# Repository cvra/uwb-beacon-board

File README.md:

# Universal beacon system board

This repository holds the schematics and layout of a board used as beacon localisation system for Eurobot.
It uses an Ultra-Wide Band module from Decawave and IMU.

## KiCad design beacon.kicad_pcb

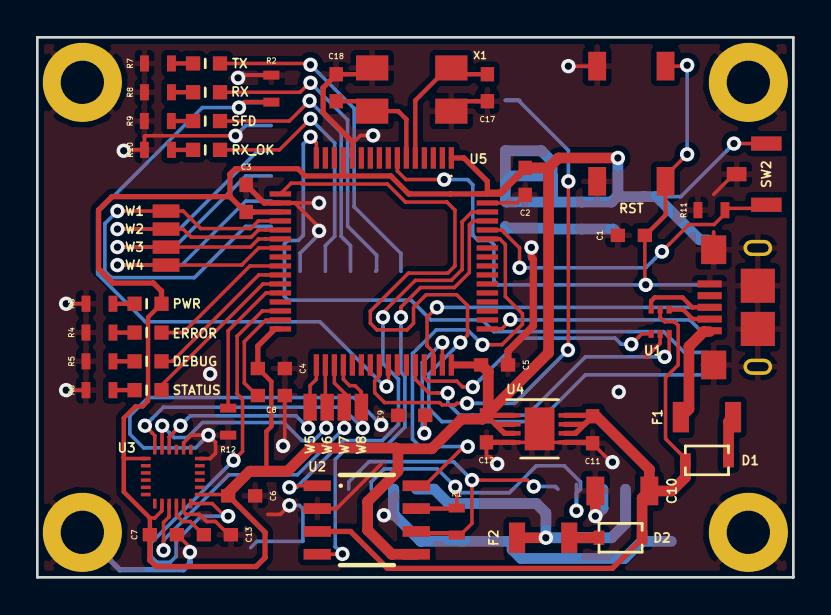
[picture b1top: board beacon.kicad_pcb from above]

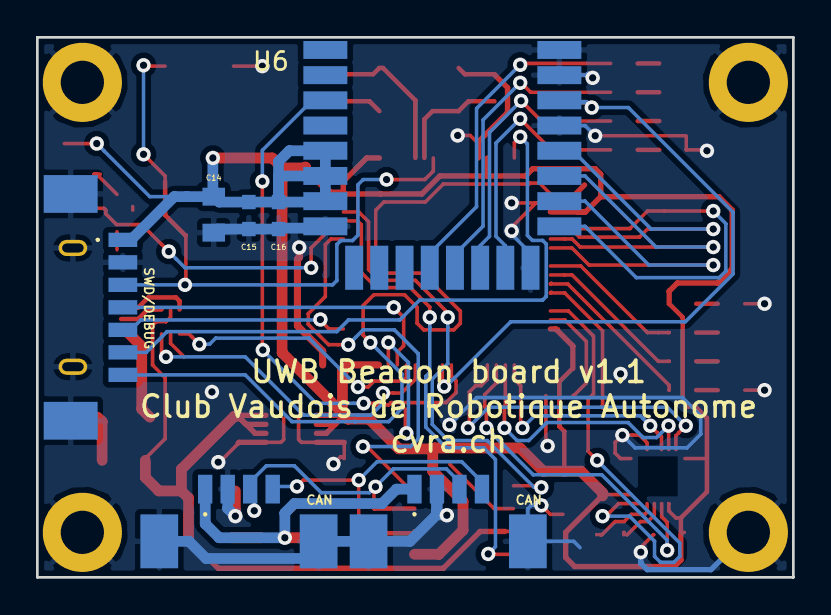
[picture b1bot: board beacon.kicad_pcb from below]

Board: 2 copper layers, 42.0 x 30.0 mm, 67 parts (7 on the bottom side), 54 nets.

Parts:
C1, C3, C4, C5, C6, C13, C16: 0.1uF; C_0603
C2, C15: 4.7uF; C_0603
C7: 10nF; C_0603
C8, C9: 2.2uF; C_0603
C10: 100uF; C_1206
C11, C12: 10uF; C_0603
C14: 47uF; C_0805
C17, C18: 10pF; C_0603
CONN1: MICRO_USB; _Micro-USB-AB-receptacle-SMT-th
CONN2, CONN3: CAN; _Molex-PicoBlade-SMD-4
CONN4: SWD/DEBUG; _Molex-PicoBlade-SMD-7
D1, D2: SBR130S3-7; _SOD-323
D3: PWR; D_0603
D4: ERROR; D_0603
D5: DEBUG; D_0603
D6: STATUS; D_0603
D7: TX; D_0603
D8: RX; D_0603
D9: SFD; D_0603
D10: RX_OK; D_0603
F1, F2: 0ZCJ0050AF2E; R_1206
H1, H2, H3, H4: M2_HOLE; _M2
R1: 120; R_0603
R2, R11, R12: 10k; R_0603
R3, R4, R5, R6, R7, R8, R9, R10: 330; R_0603
SW1: RST; _PTS525SK15-SMT-Pushbutton
SW2: DFU; SMD_Pushbutton_B3U-3100P
U1: NUF2042XV6; SOT-563_6-lead
U2: SN65HVD256; _SO-8
U3: MPU-9250; _MPU-9XX0
U4: LT1965-3.3; DFN-8-1EP_3x3mm_Pitch0.5mm
U5: STM32F405RGT6; _LQFP64
U6: DWM1000
W1: TEST_UWB_CSN; Test_1pin_SMD
W2: TEST_UWB_CLK; Test_1pin_SMD
W3, W7: TEST_UWB_MISO; Test_1pin_SMD
W4, W8: TEST_UWB_MOSI; Test_1pin_SMD
W5: TEST_IMU_CSN; Test_1pin_SMD
W6: TEST_UWB_SCK; Test_1pin_SMD
X1: 16MHz; XTAL_ABMM2

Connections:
+5V_protected: C10.1, C11.1, D1.1, D2.1, U1.5, U2.3, U4.6, U4.7, U4.8
/BOOT0: R11.2, SW2.1, U5.60
/BOOT1: R12.2, U5.28
/CAN1_RX: U2.4, U5.61
/CAN1_SILENT: U2.8, U5.59
/CAN1_TX: U2.1, U5.62
/DEBUG_LED: D5.2, U5.26
/ERROR_LED: D4.2, U5.25
/IMU_CS_N: U3.22, U5.33, W5.1
/IMU_INT: U3.12, U5.30
/IMU_MISO: U3.9, U5.35, W7.1
/IMU_MOSI: U3.24, U5.36, W8.1
/IMU_SCK: U3.23, U5.34, W6.1
/STATUS_LED: D6.2, U5.27
/STM32_NRST: C1.1, CONN4.3, SW1.2, U5.7
/STM32_SWCLK: CONN4.5, U5.49
/STM32_SWDIO: CONN4.4, U5.46
/UART_RX: CONN4.7, U5.17
/UART_TX: CONN4.6, U5.16
/USB_DM: U1.3, U5.44
/USB_DP: U1.1, U5.45
/UWB_CLK: U5.21, U6.20, W2.1
/UWB_CS_N: U5.20, U6.17, W1.1
/UWB_IRQ: R2.2, U5.41, U6.22
/UWB_MISO: U5.22, U6.19, W3.1
/UWB_MOSI: U5.23, U6.18, W4.1
/UWB_RST_N: U5.40, U6.3
/UWB_RX: D8.2, U6.13
/UWB_RX_OK: D10.2, U6.15
/UWB_SFD: D9.2, U6.14
/UWB_TX: D7.2, U6.12
GND: C1.2, C2.2, C3.2, C4.2, C5.2, C6.2, C7.2, C8.2, C9.2, C10.2, C11.2, C12.2, C13.2, C14.2, C15.2, C16.2, C17.2, C18.2, CONN1.5, CONN1.6, CONN2.2, CONN2.MECH, CONN3.2, CONN3.MECH, CONN4.2, CONN4.MECH, H1.1, H2.1, H3.1, H4.1, R2.1, R3.1, R4.1, R5.1, R6.1, R7.1, R8.1, R9.1, R10.1, R11.1, R12.1, SW1.1, SW2.3, U1.2, U2.2, U3.11, U3.18, U3.20, U4.4, U4.5, U4.9, U5.12, U5.18, U5.63, U6.8, U6.16, U6.21, U6.23, U6.24, X1.2, X1.4
unnamed: C8.1, U5.31
unnamed: C9.1, U5.47
unnamed: C13.1, U3.10
unnamed: C17.1, U5.5, X1.1
unnamed: C18.1, U5.6, X1.3
unnamed: CONN1.1, F1.1
unnamed: CONN1.2, U1.4
unnamed: CONN1.3, U1.6
unnamed: CONN2.1, CONN3.1, F2.1
unnamed: CONN2.3, CONN3.3, R1.1, U2.7
unnamed: CONN2.4, CONN3.4, R1.2, U2.6
unnamed: D1.2, F1.2
unnamed: D2.2, F2.2
unnamed: D3.1, R3.2
unnamed: D4.1, R4.2
unnamed: D5.1, R5.2
unnamed: D6.1, R6.2
unnamed: D7.1, R7.2
unnamed: D8.1, R8.2
unnamed: D9.1, R9.2
unnamed: D10.1, R10.2
VCC: C2.1, C3.1, C4.1, C5.1, C6.1, C7.1, C12.1, C14.1, C15.1, C16.1, CONN4.1, D3.2, SW2.2, U2.5, U3.1, U3.8, U3.13, U4.1, U4.2, U4.3, U5.1, U5.13, U5.19, U5.32, U5.48, U5.64, U6.5, U6.6, U6.7

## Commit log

2016-06-22 Add CVRA parts library
2016-06-22 Setup KiCad project with libraries
2016-06-22 Add MCU, oscillator and debug connector
2016-06-23 Add Decawave 1000 module
2016-06-23 Add USB
2016-06-23 Add IMU
2016-06-23 Add CAN interface
2016-06-23 Add missing datasheets
2016-06-23 Add power regulator for VCC 3.3V
2016-06-23 Choose an appropriate PTC resettable fuse
2016-06-23 Add debug leds, logo & plot pdf
2016-06-23 Annotate schematic
    Also added missing capacitors on MCU
2016-06-23 Add a readme
2016-06-24 Update with first corrections from review
    Add reset button
    Fix CAN wiring
    Add test pads on SPI buses
    Fix MCU pin name
2016-06-26 Update with further corrections from review
    LED resistors 330 so we sink ~3mA at 3.3V
    Fix NUF2042XV6 name
    Fix MPU9205 wiring (contradictory datasheet)
2016-06-28 Place components, first try
2016-06-28 Update component placement
2016-06-28 Add mounting holes and fix testpads
2016-06-28 Add logo
2016-06-29 Route PCB
2016-07-04 Generate gerber files
2016-07-13 Correct PCB routing from review remarks
    - MPU9250 footprint
    - Missing vias for good ground
2016-07-20 Corrections from review remarks
2017-12-21 Add board dimensions to README
2018-01-13 Rewire UWB reset to not interfere with VUSB sense
    Fixes #2
2018-02-03 Make it possible to boot from DFU
    Fixes #1
2018-02-03 Move status LED pins
2018-02-03 Move UWB reset from USB ID to PC9
2018-02-04 Generate pdf of schematics
2018-02-04 Update netlist/layout
2018-02-20 Minor changes to gerber before prod
